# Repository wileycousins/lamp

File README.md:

# lamp
Another object from [Wiley Cousins](https://wileycousins.com) and [Trig Projects](http://trigprojects.com)

Lamp is a smart LED lamp system that has two jobs: letting you know about things and looking pretty. Currently in development.

## requirements
* Node.js
* Foreman

## setup
    npm install

## running
    foreman start

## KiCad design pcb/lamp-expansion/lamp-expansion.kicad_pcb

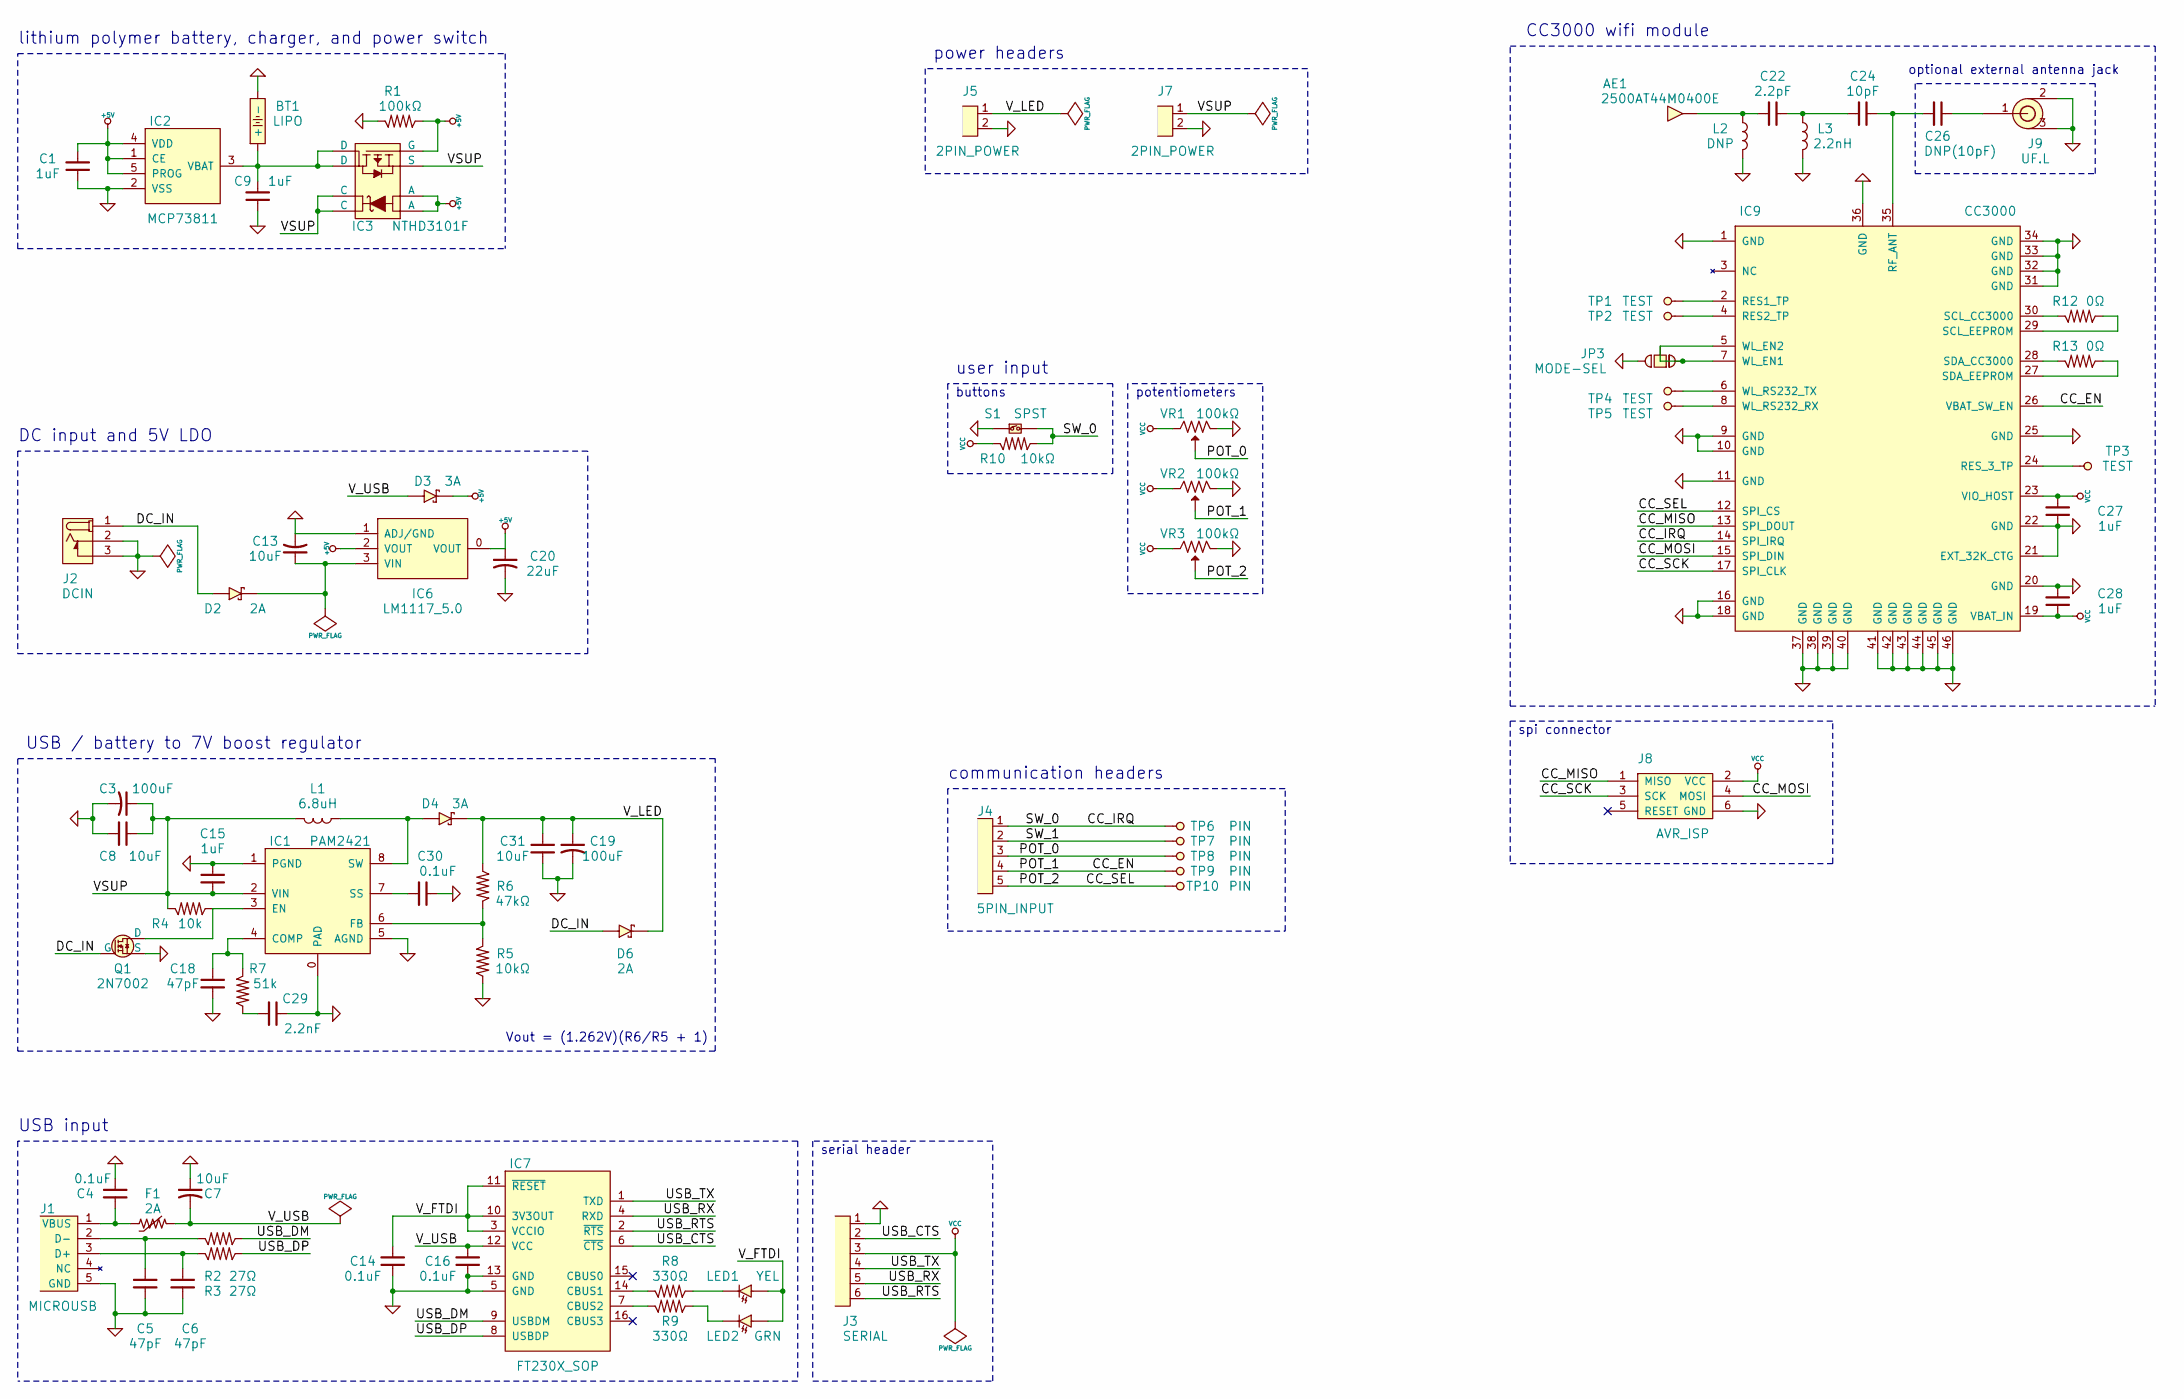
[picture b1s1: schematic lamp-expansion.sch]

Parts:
AE1: 2500AT44M0400E; Manuf. Part 2500AT44M0400E
BT1: LIPO
C1, C9, C15, C27, C28: 1uF
C3, C19: 100uF; Manuf. Part EMVA160ADA101MF55G
C4, C14, C16, C30: 0.1uF
C5, C6, C18: 47pF
C7: 10uF; Manuf. Part Taiyo Yuden
C8, C31: 10uF
C13: 10uF; Manuf. Part TMK316F106ZL-T
C20: 22uF; Manuf. Part LMK316F226ZL-T
C22: 2.2pF
C24: 10pF
C26: DNP(10pF)
C29: 2.2nF
D2, D6: 2A; Manuf. Part MSS2P2-M3/89A
D3, D4: 3A; Manuf. Part RB056L-40TE25
F1: 2A
IC1: PAM2421
IC2: MCP73811; Manuf. Part MCP73811T-420I/OT
IC3: NTHD3101F
IC6: LM1117_5.0; Manuf. Part AZ1117CH-5.0TRG1
IC7: FT230X_SOP
IC9: CC3000; Manuf. Part CC3000MOD
J1: MICROUSB
J2: DCIN
J3: SERIAL
J4: 5PIN_INPUT
J5, J7: 2PIN_POWER
J8: AVR_ISP
J9: UF.L
JP3: MODE-SEL
L1: 6.8uH; Manuf. Part SRN6045-6R8Y
L2: DNP
L3: 2.2nH
LED1: YEL
LED2: GRN
Q1: 2N7002; Manuf. Part 2N7002P,215
R1: 100kΩ
R2, R3: 27Ω
R4: 10k
R5, R10: 10kΩ
R6: 47kΩ
R7: 51k
R8, R9: 330Ω
R12, R13: 0Ω
S1: SPST
TP1, TP2, TP3, TP4, TP5: TEST
TP6, TP7, TP8, TP9, TP10: PIN
VR1, VR2, VR3: 100kΩ; Manuf. Part PTA2043-2015CPB103

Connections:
+5V: C1.1, C20.1, D3.1 (C), IC2.1 (CE), IC2.4 (VDD), IC2.5 (PROG), IC3.1 (A), IC3.2 (A), IC3.4 (G), IC6.0 (VOUT), IC6.2 (VOUT), R1.2
/CC_EN: IC9.26 (VBAT_SW_EN), J4.4, TP9.1, VR2.2 (W)
/CC_IRQ: IC9.14 (SPI_IRQ), J4.1, R10.2, S1.2, TP6.1
/CC_MISO: IC9.13 (SPI_DOUT), J8.1 (MISO)
/CC_MOSI: IC9.15 (SPI_DIN), J8.4 (MOSI)
/CC_SCK: IC9.17 (SPI_CLK), J8.3 (SCK)
/CC_SEL: IC9.12 (SPI_CS), J4.5, TP10.1, VR3.2 (W)
/DC_IN: D2.2 (A), D6.2 (A), J2.1 (POLE), Q1.1 (G)
/POT_0: J4.3, TP8.1, VR1.2 (W)
/SW_1: J4.2, TP7.1
/USB_CTS: IC7.6 (~CTS~), J3.2
/USB_DM: IC7.9 (USBDM), R2.2
/USB_DP: IC7.8 (USBDP), R3.2
/USB_RTS: IC7.2 (~RTS~), J3.6
/USB_RX: IC7.4 (RXD), J3.5
/USB_TX: IC7.1 (TXD), J3.4
/VSUP: C3.1, C8.1, C15.2, IC1.2 (VIN), IC3.3 (S), IC3.7 (C), IC3.8 (C), J7.1, L1.2, R4.1
/V_FTDI: C14.1, IC7.3 (VCCIO), IC7.10 (3V3OUT), IC7.11 (~RESET~), LED1.2 (A), LED2.2 (A)
/V_LED: C19.1, C31.1, D4.1 (C), D6.1 (C), J5.1, R6.2
/V_USB: C7.2, C16.1, D3.2 (A), F1.2, IC7.12 (VCC)
GND: BT1.2 (-), C1.2, C3.2, C4.1, C5.2, C6.2, C7.1, C8.2, C9.2, C13.2, C14.2, C15.1, C16.2, C18.2, C19.2, C20.2, C27.2, C28.1, C29.1, C30.2, C31.2, IC1.0 (PAD), IC1.1 (PGND), IC1.5 (AGND), IC2.2 (VSS), IC6.1 (ADJ/GND), IC7.5 (GND), IC7.13 (GND), IC9.1 (GND), IC9.9 (GND), IC9.10 (GND), IC9.11 (GND), IC9.16 (GND), IC9.18 (GND), IC9.20 (GND), IC9.21 (EXT_32K_CTG), IC9.22 (GND), IC9.25 (GND), IC9.31 (GND), IC9.32 (GND), IC9.33 (GND), IC9.34 (GND), IC9.36 (GND), IC9.37 (GND), IC9.38 (GND), IC9.39 (GND), IC9.40 (GND), IC9.41 (GND), IC9.42 (GND), IC9.43 (GND), IC9.44 (GND), IC9.45 (GND), IC9.46 (GND), J1.5 (GND), J2.2 (OUT), J2.3 (OUT), J3.1, J5.2, J7.2, J8.6 (GND), J9.2, J9.3, JP3.3, L2.2, L3.2, Q1.2 (S), R1.1, R5.2, S1.1, VR1.3 (E2), VR2.3 (E2), VR3.3 (E2)
unnamed: AE1.1, C22.1, L2.1
unnamed: BT1.1 (+), C9.1, IC2.3 (VBAT), IC3.5 (D), IC3.6 (D)
unnamed: C4.2, F1.1, J1.1 (VBUS)
unnamed: C5.1, J1.2 (D-), R2.1
unnamed: C6.1, J1.3 (D+), R3.1
unnamed: C13.1, D2.1 (C), IC6.3 (VIN)
unnamed: C18.1, IC1.4 (COMP), R7.1
unnamed: C22.2, C24.2, L3.1
unnamed: C24.1, C26.1, IC9.35 (RF_ANT)
unnamed: C26.2, J9.1 (CENTER)
unnamed: C29.2, R7.2
unnamed: C30.1, IC1.7 (SS)
unnamed: D4.2 (A), IC1.8 (SW), L1.1
unnamed: IC1.3 (EN), Q1.3 (D), R4.2
unnamed: IC1.6 (FB), R5.1, R6.1
unnamed: IC7.7 (CBUS2), R9.1
unnamed: IC7.14 (CBUS1), R8.1
unnamed: IC9.2 (RES1_TP), TP1.1
unnamed: IC9.4 (RES2_TP), TP2.1
unnamed: IC9.5 (WL_EN2), IC9.7 (WL_EN1), JP3.1, JP3.2
unnamed: IC9.6 (WL_RS232_TX), TP4.1
unnamed: IC9.8 (WL_RS232_RX), TP5.1
unnamed: IC9.24 (RES_3_TP), TP3.1
unnamed: IC9.27 (SDA_EEPROM), R13.2
unnamed: IC9.28 (SDA_CC3000), R13.1
unnamed: IC9.29 (SCL_EEPROM), R12.2
unnamed: IC9.30 (SCL_CC3000), R12.1
unnamed: LED1.1 (C), R8.2
unnamed: LED2.1 (C), R9.2
VCC: C27.1, C28.2, IC9.19 (VBAT_IN), IC9.23 (VIO_HOST), J3.3, J8.2 (VCC), R10.1, VR1.1 (E1), VR2.1 (E1), VR3.1 (E1)

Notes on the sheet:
USB input
DC input and 5V LDO
lithium polymer battery, charger, and power switch
optional external antenna jack
CC3000 wifi module
spi connector
USB / battery to 7V boost regulator
power headers
serial header
potentiometers
buttons
user input
Vout = (1.262V)(R6/R5 + 1)
communication headers

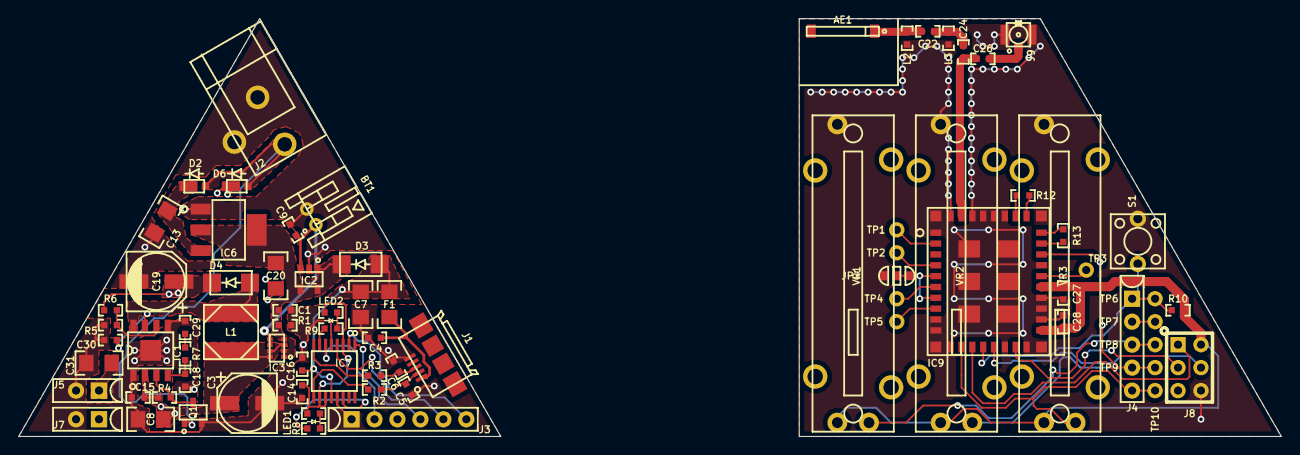
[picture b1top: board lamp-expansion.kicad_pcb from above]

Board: 2 copper layers, 139.7 x 46.2 mm, 77 parts (0 on the bottom side), 51 nets.

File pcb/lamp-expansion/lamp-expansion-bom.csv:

Source:,/media/sf_projects/lamp/pcb/lamp-expansion/lamp-expansion.sch
Date:,Fri 15 Aug 2014 06:17:15 PM CDT
Tool:,Eeschema (2014-04-22 BZR 4817)-product
Component Count:,67

Individual Components:

Item,Qty,Reference(s),Value,LibPart,Footprint,Datasheet,Distrib. Part,Distributor,Manuf. Part,Manufacturer
,,AE1,2500AT44M0400E,standard:ANTENNA,,,712-1403-1-ND,Digikey,2500AT44M0400E,Johanson Technology Inc
,,BT1,LIPO,connector:LIPO,,,,,,
,,C1,1uF,standard:C,,,,,,
,,C13,10uF,standard:C_POL,,,587-1353-1-ND,Digikey,TMK316F106ZL-T,Taiyo Yuden
,,C14,0.1uF,standard:C,,,,,,
,,C15,1uF,standard:C,,,,,,
,,C16,0.1uF,standard:C,,,,,,
,,C18,47pF,standard:C,,,,,,
,,C19,100uF,standard:C_POL,,,565-2089-1-ND,Digikey,EMVA160ADA101MF55G,United Chemi-Con
,,C20,22uF,standard:C_POL,,,587-1356-1-ND,Digikey,LMK316F226ZL-T,Taiyo Yuden
,,C22,2.2pF,standard:C,,,,,,
,,C24,10pF,standard:C,,,,,,
,,C26,DNP(10pF),standard:C,,,,,,
,,C27,1uF,standard:C,,,,,,
,,C28,1uF,standard:C,,,,,,
,,C29,2.2nF,standard:C,,,,,,
,,C3,100uF,standard:C_POL,,,565-2089-1-ND,Digikey,EMVA160ADA101MF55G,United Chemi-Con
,,C30,0.1uF,standard:C,,,,,,
,,C31,10uF,standard:C,,,,,,
,,C4,0.1uF,standard:C,,,,,,
,,C5,47pF,standard:C,,,,,,
,,C6,47pF,standard:C,,,,,,
,,C7,10uF,standard:C_POL,,,587-1353-1-ND,Digikey,Taiyo Yuden,TMK316F106ZL-T
,,C8,10uF,standard:C,,,,,,
,,C9,1uF,standard:C,,,,,,
,,D2,2A,standard:D_SCHOTTKY,,,MSS2P2-M3/89AGICT-ND,Digikey,MSS2P2-M3/89A,Vishay
,,D3,3A,standard:D_SCHOTTKY,,,RB056L-40TE25CT-ND,Digikey,RB056L-40TE25,Rohm Semiconductor
,,D4,3A,standard:D_SCHOTTKY,,,RB056L-40TE25CT-ND,Digikey,RB056L-40TE25,Rohm Semiconductor
,,D6,2A,standard:D_SCHOTTKY,,,MSS2P2-M3/89AGICT-ND,Digikey,MSS2P2-M3/89A,Vishay
,,F1,2A,standard:PTC,,,,,,
,,IC1,PAM2421,diode-inc-ic:PAM242X,,,,,,Diodes Inc
,,IC2,MCP73811,microchip-ic:MCP73811/2,,,MCP73811T-420I/OTCT-ND,Digikey,MCP73811T-420I/OT,Microchip Technology
,,IC3,NTHD3101F,on-semi-ic:NTHD3101F,,,,,,On Semiconductor
,,IC6,LM1117_5.0,regulator:LM1117,,,AZ1117CH-5.0TRG1DICT-ND,Digikey,AZ1117CH-5.0TRG1,Diodes Incorporated
,,IC7,FT230X_SOP,ftdi-ic:FT230X_SOP,,,,,,
,,IC9,CC3000,ti-ic:CC3000,,http://www.ti.com/lit/gpn/cc3000,296-35512-1-ND,Digikey,CC3000MOD,TI
,,J1,MICROUSB,connector:MICROUSB,,,,,,
,,J2,DCIN,connector:DC-BARREL-JACK,,,,,,
,,J3,SERIAL,connector:6PIN_FEMALE,,,,,,
,,J4,5PIN_INPUT,connector:5PIN_FEMALE,,,,,,
,,J5,2PIN_POWER,connector:2PIN_FEMALE,,,,,,
,,J7,2PIN_POWER,connector:2PIN_FEMALE,,,,,,
,,J8,AVR_ISP,avr-mcu:AVR_ISP,,,,,,
,,J9,UF.L,connector:COAX-JACK,,,,,,
,,JP3,MODE-SEL,standard:JUMPER_3-PIN,,,,,,
,,L1,6.8uH,standard:L,,,SRN6045-6R8YCT-ND,Digikey,SRN6045-6R8Y,Bourns Inc
,,L2,DNP,standard:L,,,,,,
,,L3,2.2nH,standard:L,,,,,,
,,LED1,YEL,standard:LED,,,,,,
,,LED2,GRN,standard:LED,,,,,,
,,Q1,2N7002,transistor:N-CHAN-MOSFET_SOT,,,568-5818-1-ND,Digikey,"2N7002P,215",NXP

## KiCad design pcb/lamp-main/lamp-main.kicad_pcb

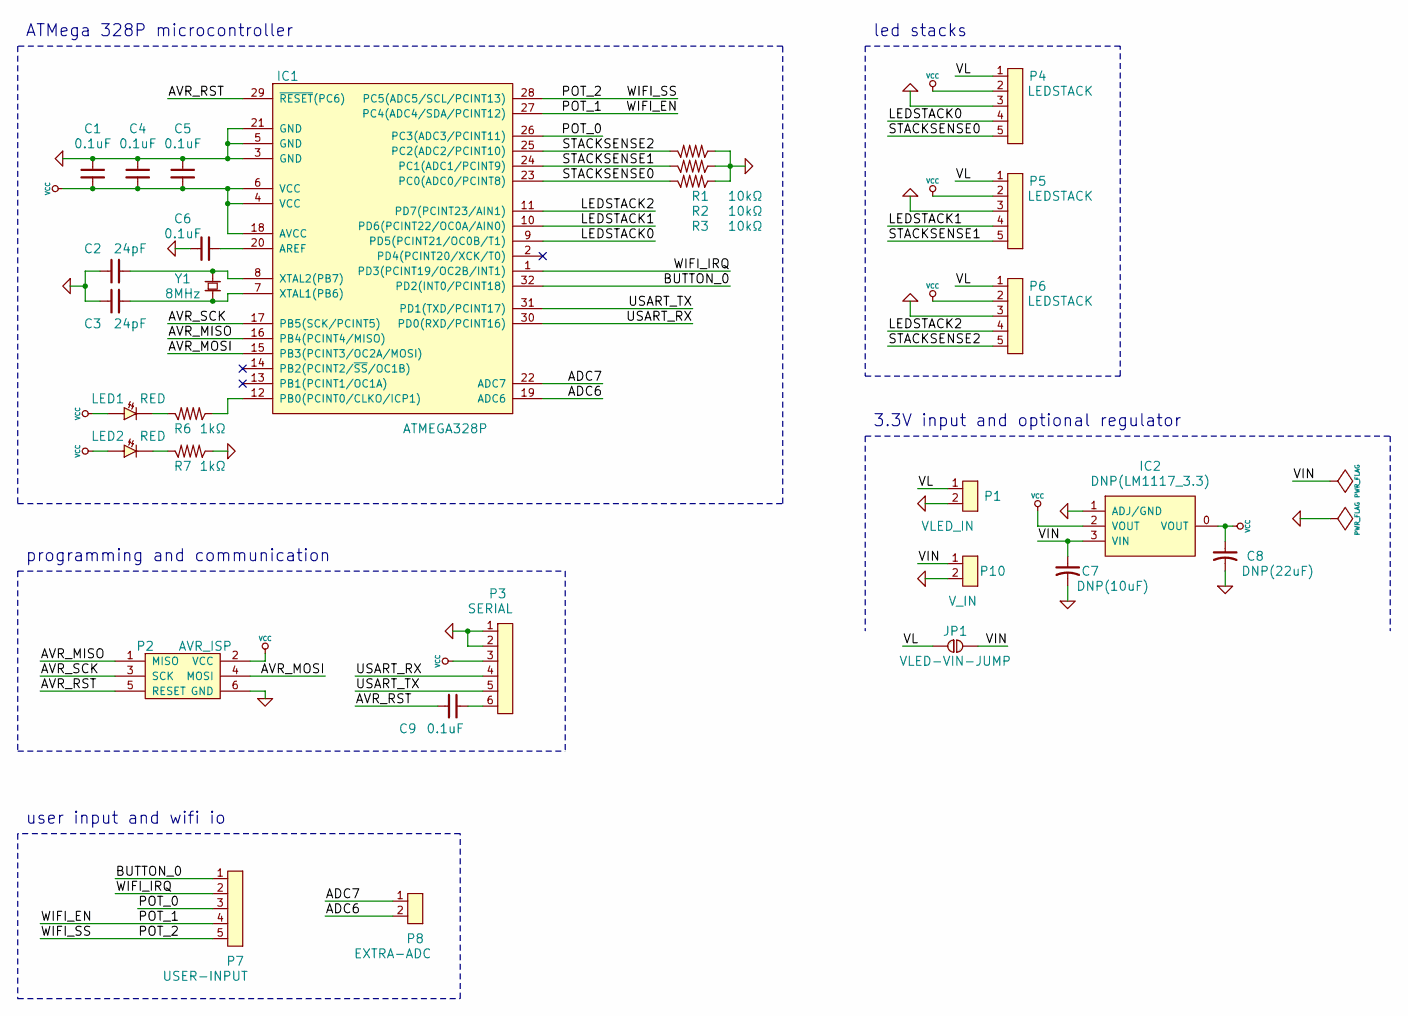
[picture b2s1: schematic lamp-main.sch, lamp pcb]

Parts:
C1, C4, C5, C6, C9: 0.1uF
C2, C3: 24pF; Manuf. Part CL10C240JB8NCNC
C7: DNP(10uF); Manuf. Part TMK316F106ZL-T
C8: DNP(22uF); Manuf. Part LMK316F226ZL-T
IC1: ATMEGA328P; Manufacturer Part ATMEGA328P-AU
IC2: DNP(LM1117_3.3); Manuf. Part AZ1117CH-5.0TRG1
JP1: VLED-VIN-JUMP
LED1, LED2: RED
P1: VLED_IN
P2: AVR_ISP
P3: SERIAL
P4, P5, P6: LEDSTACK
P7: USER-INPUT
P8: EXTRA-ADC
P10: V_IN
R1, R2, R3: 10kΩ
R6, R7: 1kΩ
Y1: 8MHz; Manuf. Part ABM2-8.000MHZ-D4Y-T

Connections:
/ADC6: IC1.19 (ADC6), P8.2
/ADC7: IC1.22 (ADC7), P8.1
/AVR_MISO: IC1.16 (PB4(PCINT4/MISO)), P2.1 (MISO)
/AVR_MOSI: IC1.15 (PB3(PCINT3/OC2A/MOSI)), P2.4 (MOSI)
/AVR_RST: C9.1, IC1.29 (~RESET~(PC6)), P2.5 (RESET)
/AVR_SCK: IC1.17 (PB5(SCK/PCINT5)), P2.3 (SCK)
/BUTTON_0: IC1.32 (PD2(INT0/PCINT18)), P7.1
/LEDSTACK0: IC1.9 (PD5(PCINT21/OC0B/T1)), P4.4
/LEDSTACK1: IC1.10 (PD6(PCINT22/OC0A/AIN0)), P5.4
/LEDSTACK2: IC1.11 (PD7(PCINT23/AIN1)), P6.4
/POT_0: IC1.26 (PC3(ADC3/PCINT11)), P7.3
/POT_1: IC1.27 (PC4(ADC4/SDA/PCINT12)), P7.4
/POT_2: IC1.28 (PC5(ADC5/SCL/PCINT13)), P7.5
/STACKSENSE0: IC1.23 (PC0(ADC0/PCINT8)), P4.5, R3.1
/STACKSENSE1: IC1.24 (PC1(ADC1/PCINT9)), P5.5, R2.1
/STACKSENSE2: IC1.25 (PC2(ADC2/PCINT10)), P6.5, R1.1
/USART_RX: IC1.30 (PD0(RXD/PCINT16)), P3.4
/USART_TX: IC1.31 (PD1(TXD/PCINT17)), P3.5
/VIN: C7.1, IC2.3 (VIN), JP1.2, P10.1
/VL: JP1.1, P1.1, P4.1, P5.1, P6.1
/WIFI_IRQ: IC1.1 (PD3(PCINT19/OC2B/INT1)), P7.2
GND: C1.2, C2.1, C3.1, C4.2, C5.2, C6.1, C7.2, C8.2, IC1.3 (GND), IC1.5 (GND), IC1.21 (GND), IC2.1 (ADJ/GND), P1.2, P2.6 (GND), P3.1, P3.2, P4.3, P5.3, P6.3, P10.2, R1.2, R2.2, R3.2, R7.2
unnamed: C2.2, IC1.8 (XTAL2(PB7)), Y1.2
unnamed: C3.2, IC1.7 (XTAL1(PB6)), Y1.1
unnamed: C6.2, IC1.20 (AREF)
unnamed: C9.2, P3.6
unnamed: IC1.12 (PB0(PCINT0/CLKO/ICP1)), R6.2
unnamed: LED1.1 (C), R6.1
unnamed: LED2.1 (C), R7.1
VCC: C1.1, C4.1, C5.1, C8.1, IC1.4 (VCC), IC1.6 (VCC), IC1.18 (AVCC), IC2.0 (VOUT), IC2.2 (VOUT), LED1.2 (A), LED2.2 (A), P2.2 (VCC), P3.3, P4.2, P5.2, P6.2

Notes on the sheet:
3.3V input and optional regulator
programming and communication
led stacks
ATMega 328P microcontroller
user input and wifi io

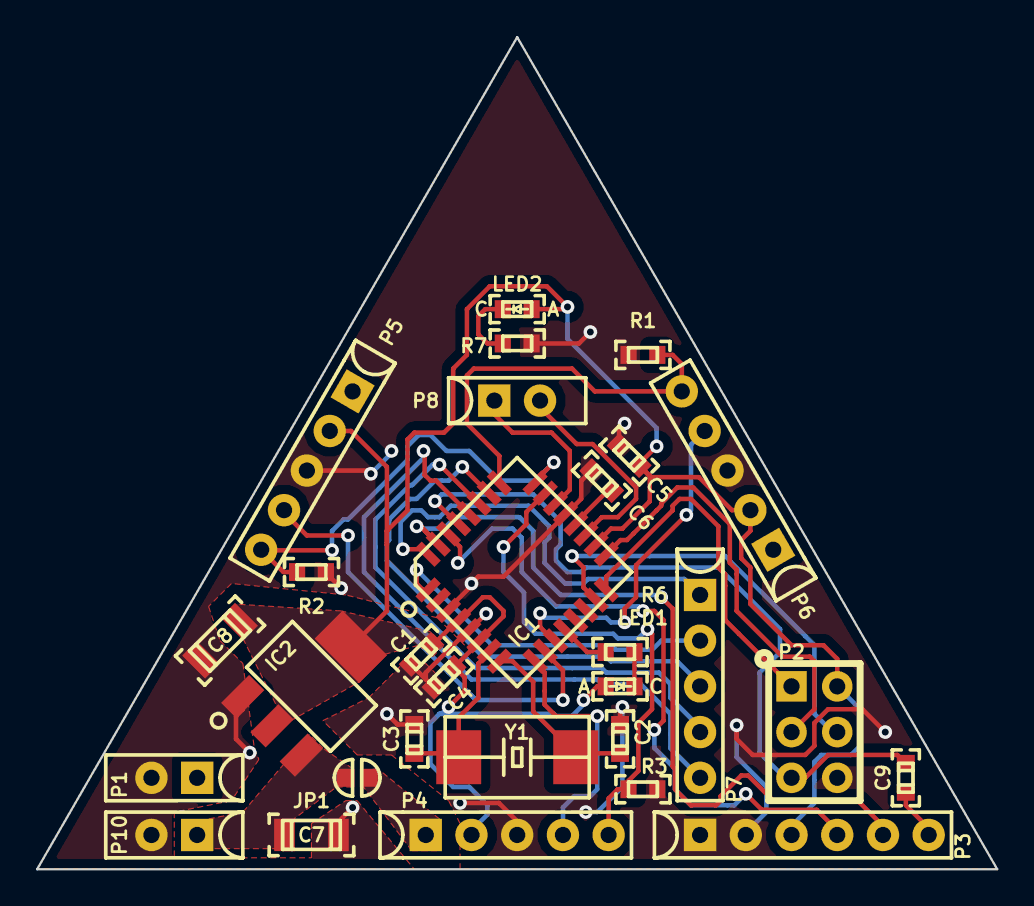
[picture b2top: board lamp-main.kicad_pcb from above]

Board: 2 copper layers, 53.3 x 46.2 mm, 29 parts (0 on the bottom side), 30 nets.

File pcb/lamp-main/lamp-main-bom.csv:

Source:,/media/sf_projects/lamp/pcb/lamp-main/lamp-main.sch
Date:,Fri 15 Aug 2014 04:16:45 PM CDT
Tool:,eeschema (2014-03-19 BZR 4756)-product
Component Count:,29

Individual Components:

Item,Qty,Reference(s),Value,LibPart,Footprint,Datasheet,Distrib. Link,Distrib. Part,Distributor,Manuf. Part,Manufacturer
,,C1,0.1uF,standard:C,capacitor:0603(1608m)-CHIP-CAP,,,,On Hand,,
,,C2,24pF,standard:C,capacitor:0603(1608m)-CHIP-CAP,,http://www.digikey.com/product-detail/en/CL10C240JB8NCNC/127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,1276-2242-1-ND,Digikey,CL10C240JB8NCNC,Samsung
,,C3,24pF,standard:C,capacitor:0603(1608m)-CHIP-CAP,,http://www.digikey.com/product-detail/en/CL10C240JB8NCNC/127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,1276-2242-1-ND,Digikey,CL10C240JB8NCNC,"Samsung Electro-Mechanics America, Inc"
,,C4,0.1uF,standard:C,capacitor:0603(1608m)-CHIP-CAP,,,,On hand,,
,,C5,0.1uF,standard:C,capacitor:0603(1608m)-CHIP-CAP,,,,On hand,,
,,C6,0.1uF,standard:C,capacitor:0603(1608m)-CHIP-CAP,,,,On hand,,
,,C7,DNP(10uF),standard:C_POL,capacitor:1206(3216m)-CHIP-CAP,,http://www.digikey.com/product-detail/en/TMK316F106ZL-T/587-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,587-1353-1-ND,Digikey,TMK316F106ZL-T,Taiyo Yuden
,,C8,DNP(22uF),standard:C_POL,capacitor:1206(3216m)-CHIP-CAP,,http://www.digikey.com/product-detail/en/LMK316F226ZL-T/587-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,587-1356-1-ND,Digikey,LMK316F226ZL-T,Taiyo Yuden
,,C9,0.1uF,standard:C,capacitor:0603(1608m)-CHIP-CAP,,,,On hand,,
,,IC1,ATMEGA328P,avr-mcu:ATMEGA328P_TQFP,qfp:TQFP32_P0.8mm,,http://www.digikey.com/product-detail/en/ATMEGA328P-AU/ATMEG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,ATMEGA328P-AU-ND,Digikey,ATMEGA328P-AU,Atmel
,,IC2,DNP(LM1117_3.3),lamp-main-cache:LM1117,sot:SOT223,http://www.diodes.com/datasheets/AZ1117C.pdf,http://www.digikey.com/product-detail/en/AZ1117CH-5.0TRG1/AZ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,AZ1117CH-5.0TRG1DICT-ND,Digikey,AZ1117CH-5.0TRG1,Diodes Incorporated
,,JP1,VLED-VIN-JUMP,standard:JUMPER_2-PIN,jumper:SOLDER-JUMPER_1-WAY,,,,,,
,,LED1,RED,standard:LED,led:0603(1608m)-SM-LED,,,,On hand,,
,,LED2,RED,standard:LED,led:0603(1608m)-SM-LED,,,,On hand,,
,,P1,VLED_IN,connector:2PIN_MALE,sip:SIP2,,,,,,
,,P10,V_IN,connector:2PIN_MALE,sip:SIP2,,,,,,
,,P2,AVR_ISP,avr-mcu:AVR_ISP,connect-thru:2x3-ARRAY_P100mil,,,,,,
,,P3,SERIAL,connector:6PIN_HEADER,sip:SIP6,,,,,,
,,P4,LEDSTACK,connector:5PIN_MALE,sip:SIP5,,,,,,
,,P5,LEDSTACK,connector:5PIN_MALE,sip:SIP5,,,,,,
,,P6,LEDSTACK,connector:5PIN_MALE,sip:SIP5,,,,,,
,,P7,USER-INPUT,connector:5PIN_MALE,sip:SIP5,,,,,,
,,P8,EXTRA-ADC,connector:2PIN_MALE,sip:SIP2,,,,,,

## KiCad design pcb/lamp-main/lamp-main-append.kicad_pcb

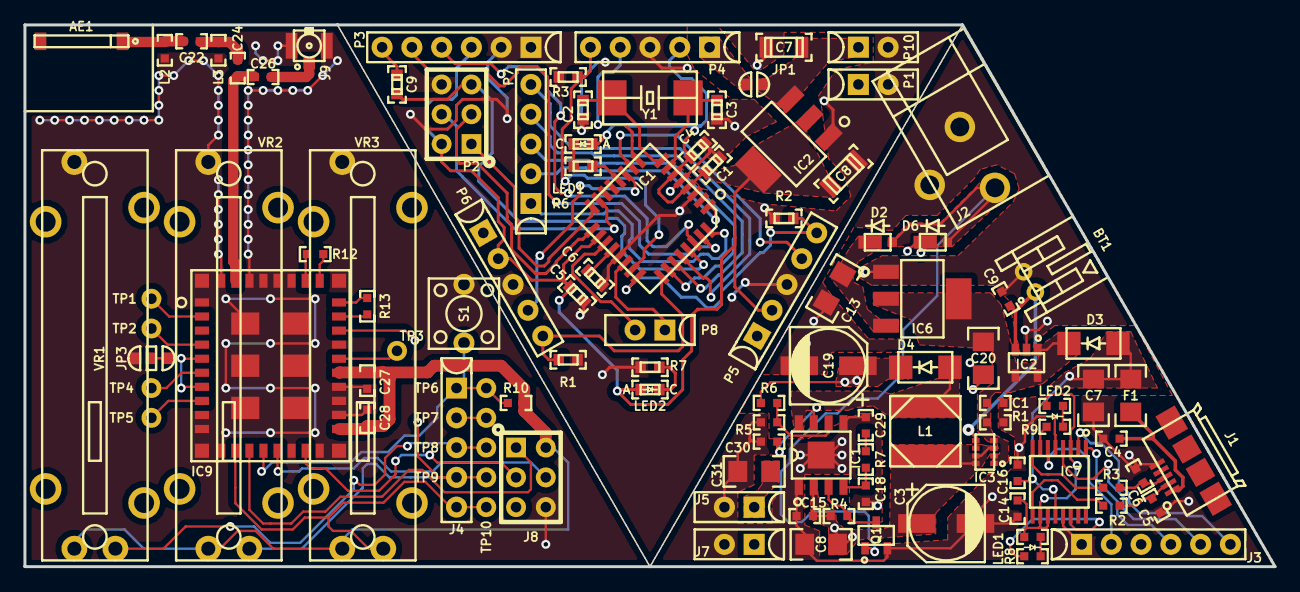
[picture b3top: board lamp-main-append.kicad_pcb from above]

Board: 2 copper layers, 106.7 x 46.2 mm, 106 parts (0 on the bottom side), 51 nets.

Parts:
AE1: 2500AT44M0400E; JOHANSON-2500AT44M0400_2.4GHz-chip-antenna
BT1: LIPO; JST-S2B-PH-K_right-angle-jack
C1, C9, C15, C27, C28: 1uF; 0603(1608m)
C1#2, C4#2, C5#2, C6#2, C9#2: 0.1uF; 0603(1608m)-CHIP-CAP
C2, C3#2: 24pF; 0603(1608m)-CHIP-CAP
C3, C19: 100uF; PANA-D_CHEMI-F_SM-ALUMINUM
C4, C14, C16, C30: 0.1uF; 0603(1608m)
C5, C6, C18: 47pF; 0603(1608m)
C7, C8, C13, C31: 10uF; 1206(3216m)
C7#2: DNP(10uF); 1206(3216m)-CHIP-CAP
C8#2: DNP(22uF); 1206(3216m)-CHIP-CAP
C20: 22uF; 1206(3216m)
C22: 2.2pF; 0603(1608m)
C24: 10pF; 0603(1608m)
C26: DNP(10pF); 0603(1608m)
C29: 2.2nF; 0603(1608m)
D2, D6: 2A; MICROSMP
D3, D4: 3A; DO-214AC
F1: 2A; 1206(3216m)
IC1: PAM2421; SOP8_ep
IC1#2: ATMEGA328P; TQFP32_P0.8mm
IC2: MCP73811; SOT23-5
IC2#2: DNP(LM1117_3.3); SOT223
IC3: NTHD3101F; CHIPFET-1206-8
IC6: LM1117_5.0; SOT223
IC7: FT230X_SOP; SSOP16
IC9: CC3000
J1: MICROUSB; MICROUSB_sm
J2: DCIN; CUI-PJ-102A_dc-barrel-jack
J3: SERIAL; SIP6
J4: 5PIN_INPUT; SIP5
J5, J7: 2PIN_POWER; SIP2
J8: AVR_ISP; 2x3-ARRAY_P100mil
J9: UF.L; U.FL-COAX
JP1: VLED-VIN-JUMP; SOLDER-JUMPER_1-WAY
JP3: MODE-SEL; SOLDER-JUMPER_2-WAY
L1: 6.8uH; SM-INDUCTOR_6mmX6mm
L2: DNP; 0603(1608m)
L3: 2.2nH; 0603(1608m)
LED1: YEL; 0603(1608m)-SM-LED
LED1#2, LED2#2: RED; 0603(1608m)-SM-LED
LED2: GRN; 0603(1608m)-SM-LED
P1: VLED_IN; SIP2
P2: AVR_ISP; 2x3-ARRAY_P100mil
P3: SERIAL; SIP6
P4, P5, P6: LEDSTACK; SIP5
P7: USER-INPUT; SIP5
P8: EXTRA-ADC; SIP2
P10: V_IN; SIP2
Q1: 2N7002; SOT23
R1: 100kΩ; 0603(1608m)
R1#2, R2#2, R3#2: 10kΩ; 0603(1608m)-CHIP-RESISTOR
R2, R3: 27Ω; 0603(1608m)
R4: 10k; 0603(1608m)
R5, R10: 10kΩ; 0603(1608m)
R6: 47kΩ; 0603(1608m)
R6#2, R7#2: 1kΩ; 0603(1608m)-CHIP-RESISTOR
R7: 51k; 0603(1608m)
R8, R9: 330Ω; 0603(1608m)
R12, R13: 0Ω; 0603(1608m)
S1: SPST; SPST-2-PIN_6mm_thru
TP1, TP2, TP3, TP4, TP5: TEST; 1-PIN
TP6, TP7, TP8, TP9, TP10: PIN; 1-PIN
VR1, VR2, VR3: 100kΩ; BOURNS-PTA2043_20mm-slide-pot
Y1: 8MHz; ABRACON-ABM2_xtal

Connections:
+5V: C1.1, C1#2.1, C4#2.1, C5#2.1, C8#2.1, C20.1, D3.1, IC1#2.4, IC1#2.6, IC1#2.18, IC2.1, IC2.4, IC2.5, IC2#2.0, IC2#2.2, IC3.1, IC3.2, IC3.4, IC6.0, IC6.2, LED1#2.2, LED2#2.2, P2.2, P3.3, P4.2, P5.2, P6.2, R1.2
/CC_EN: C1#2.2, C2.1, C3#2.1, C4#2.2, C5#2.2, C6#2.1, C7#2.2, C8#2.2, IC1#2.3, IC1#2.5, IC1#2.21, IC2#2.1, IC9.26, J4.4, P1.2, P2.6, P3.1, P3.2, P4.3, P5.3, P6.3, P10.2, R1#2.2, R2#2.2, R3#2.2, R7#2.2, TP9.1, VR2.2
/CC_IRQ: C2.2, IC1#2.8, IC9.14, J4.1, R10.2, S1.2, TP6.1, Y1.2
/CC_MISO: C3#2.2, IC1#2.7, IC9.13, J8.1, Y1.1
/CC_MOSI: C6#2.2, IC1#2.20, IC9.15, J8.4
/CC_SCK: C7#2.1, IC2#2.3, IC9.17, J8.3, JP1.2, P10.1
/CC_SEL: C9#2.1, IC1#2.29, IC9.12, J4.5, P2.5, TP10.1, VR3.2
/DC_IN: C9#2.2, D2.2, D6.2, J2.1, P3.6, Q1.1
/POT_0: IC1#2.32, J4.3, P7.1, TP8.1, VR1.2
/SW_1: IC1#2.9, J4.2, P4.4, TP7.1
/USB_CTS: IC1#2.10, IC7.6, J3.2, P5.4
/USB_DM: IC1#2.11, IC7.9, P6.4, R2.2
/USB_DP: IC1#2.12, IC7.8, R3.2, R6#2.2
/USB_RTS: IC1#2.15, IC7.2, J3.6, P2.4
/USB_RX: IC1#2.16, IC7.4, J3.5, P2.1
/USB_TX: IC1#2.17, IC7.1, J3.4, P2.3
/VSUP: C3.1, C8.1, C15.2, IC1.2, IC3.3, IC3.7, IC3.8, J7.1, L1.2, R4.1
/V_FTDI: C14.1, IC1#2.27, IC7.3, IC7.10, IC7.11, LED1.2, LED2.2, P7.4
/V_LED: C19.1, C31.1, D4.1, D6.1, IC1#2.28, J5.1, P7.5, R6.2
/V_USB: C7.2, C16.1, D3.2, F1.2, IC1#2.23, IC7.12, P4.5, R3#2.1
GND: BT1.2, C1.2, C3.2, C4.1, C5.2, C6.2, C7.1, C8.2, C9.2, C13.2, C14.2, C15.1, C16.2, C18.2, C19.2, C20.2, C27.2, C28.1, C29.1, C30.2, C31.2, IC1.0, IC1.1, IC1.5, IC1#2.24, IC2.2, IC6.1, IC7.5, IC7.13, IC9.1, IC9.9, IC9.10, IC9.11, IC9.16, IC9.18, IC9.20, IC9.21, IC9.22, IC9.25, IC9.31, IC9.32, IC9.33, IC9.34, IC9.36, IC9.37, IC9.38, IC9.39, IC9.40, IC9.41, IC9.42, IC9.43, IC9.44, IC9.45, IC9.46, J1.5, J2.2, J3.1, J5.2, J7.2, J8.6, J9.2, J9.3, JP3.3, L2.2, L3.2, P5.5, Q1.2, R1.1, R2#2.1, R5.2, S1.1, VR1.3, VR2.3, VR3.3
unnamed: AE1.1, C22.1, IC1#2.25, L2.1, P6.5, R1#2.1
unnamed: BT1.1, C9.1, IC2.3, IC3.5, IC3.6
unnamed: C4.2, F1.1, IC1#2.13, J1.1
unnamed: C5.1, IC1#2.14, J1.2, R2.1
unnamed: C6.1, IC1#2.19, J1.3, P8.2, R3.1
unnamed: C13.1, D2.1, IC6.3
unnamed: C18.1, IC1.4, IC1#2.26, P7.3, R7.1
unnamed: C22.2, C24.2, IC1#2.30, L3.1, P3.4
unnamed: C24.1, C26.1, IC1#2.31, IC9.35, P3.5
unnamed: C26.2, J9.1, LED1#2.1, R6#2.1
unnamed: C29.2, LED2#2.1, R7.2, R7#2.1
unnamed: C30.1, IC1.7, IC1#2.2
unnamed: D4.2, IC1.8, IC1#2.22, L1.1, P8.1
unnamed: IC1.3, JP1.1, P1.1, P4.1, P5.1, P6.1, Q1.3, R4.2
unnamed: IC1.6, IC1#2.1, P7.2, R5.1, R6.1
unnamed: IC7.7, R9.1
unnamed: IC7.14, R8.1
unnamed: IC9.2, TP1.1
unnamed: IC9.4, TP2.1
unnamed: IC9.5, IC9.7, JP3.1, JP3.2
unnamed: IC9.6, TP4.1
unnamed: IC9.8, TP5.1
unnamed: IC9.24, TP3.1
unnamed: IC9.27, R13.2
unnamed: IC9.28, R13.1
unnamed: IC9.29, R12.2
unnamed: IC9.30, R12.1
unnamed: LED1.1, R8.2
unnamed: LED2.1, R9.2
VCC: C27.1, C28.2, IC9.19, IC9.23, J3.3, J8.2, R10.1, VR1.1, VR2.1, VR3.1

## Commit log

2014-02-25 towel obtained
2014-02-25 basic README
2014-02-25 basic LICENSE
2014-02-26 kicad project file
2014-02-26 component libraries loaded
2014-02-26 schematic page formatting
2014-02-26 MCU set up with programming and serial headers
2014-02-26 got an led driver on there
2014-02-26 put a basic volatge regulator on there. may switch it out for something else
2014-02-27 first pass at schematic done
2014-02-27 stopping point because of new kicad library issues
2014-02-28 footprint selection done; moving to layout
2014-02-28 schematic pdf
2014-02-28 board geometry mostly figured out
2014-03-05 component positions good. need some mounting holes
2014-03-05 mounting holes
2014-03-05 laying traces
2014-03-05 layout going well but computer dying
2014-03-06 layout done. getting quotes then gonna clean up
2014-03-06 got some panelization going on for quotes
2014-03-06 done with work for the night
2014-03-06 adding some first pass gerbers. probably not good for actual fab, but sizing is right for quoting
2014-03-06 silkscreen cleaned up. need to figure out how I actually want to panelize
2014-03-06 i like this panelization layout
2014-03-13 full panel
2014-03-13 jk roflcopter. panel is now correct
2014-03-13 ok this might've finally got it
2014-03-13 fixed up board outline and fills
2014-03-13 panel plot
2014-03-13 new barebones plots
2014-03-13 barebones readme
2014-03-13 barebones order placed
2014-03-13 adding bom
2014-03-13 fixing up a few minor bom issues
2014-03-20 add first firmware files
2014-03-20 blink heartbeat led
2014-03-21 it's alive and my eyes hurt! @hcwiley
2014-03-21 cycle through colors
2014-03-21 add missing no-connect to avr pin
2014-03-21 add unused pin initilization
2014-03-21 implement led stack size sensing
2014-03-21 does not work in hardware
2014-03-21 stack sense correctly senses number of cards in stack
2014-03-21 verify that arrays are being calloced correctly and new set function works
2014-03-22 struggle bus
2014-03-22 slow but steady progress
2014-03-22 adjust data stream according to number of cards (finally)
2014-03-22 done with arduino testing sketch
2014-03-22 send data to all stacks with cards
2014-03-22 pumpz up the jamz
2014-03-26 about to go to SBSS
2014-03-30 cleanup variables
2014-03-31 figure out how to stop making this commit
2014-04-02 barebones twitter streamer working
2014-04-02 got basic mail watcher working
2014-04-02 tweet tracking updates
2014-04-02 made an index page. twitter login. w00t
2014-04-02 when you auth through twitter it starts a twitter streamer for you!
2014-04-02 i have no idea why my twitter stream is now just giving me my user obj
2014-04-02 fixed all the problems
2014-04-03 tweeter page looking pretty good. streaming working. i like this. tags addable
2014-04-03 remove tags
2014-04-03 updates to twitter tag add/remove
2014-04-03 updates from live. lamp working on webfaction
2014-04-03 added null user checks
2014-04-03 more no user checks
2014-04-03 working on profile add more services
2014-04-03 updated deploy script
2014-04-03 need username in deploy
2014-04-03 got providers working in a basic way
2014-04-03 added google auth. w00t
2014-04-03 fix title comment in header file
2014-04-03 create classes for lamp structure and effects
2014-04-03 continue work
2014-04-04 commit to move work location
2014-04-04 working on mail stream feature. also added socket disconnect that stops tweet streamer when client disconnects
2014-04-04 use pm2
2014-04-04 updated index
2014-04-04 log file names
2014-04-04 start?
2014-04-04 pull on deploy. put the logs where they should be
2014-04-04 restart?
2014-04-04 logs go where you should be
2014-04-04 what the hell pm2
2014-04-04 come on logs
2014-04-04 what ever logs, be in that dir
2014-04-04 ok lets test the restart
2014-04-04 lets keep logging killed old streamer
2014-04-04 working on memory mgmt
2014-04-04 derp
2014-04-04 moving matrix class into arduino folder for testing
2014-04-04 matrix class appears to work
2014-04-04 abandoning work on TLC class for now
2014-04-04 about to see if this compiles
2014-04-04 move to arduino testing folder for testing
2014-04-05 hold effect works
2014-04-05 add swirl effect
2014-04-05 cleanup commented out old code
2014-04-05 add rainbow effect
2014-04-16 start separating control circuits from led circuits
2014-04-21 rearranging file locations
2014-04-21 this is going somewhere
2014-04-21 move expansion board to separate project
2014-04-22 schematic work for expansion board
2014-04-22 work in progress
2014-04-22 cc3000 schematic diagram done
2014-04-22 moving to work on main board
2014-04-22 main board edits first pass done
2014-04-23 still need to add boost reg to schematic;
2014-04-23 expansion schematic nearly done
2014-04-23 i think the schematic is done
2014-04-30 schematic passes error checking
2014-04-30 ongoing footprint assignment
2014-04-30 kicad bug. building latest revision. hang on
2014-04-30 fixed typo for 74L05 LDO value
2014-05-01 assign footprints and start layout
2014-05-01 lets not stop the stream on disconnect
2014-05-01 log sending
2014-05-01 actually put it in the twitter section not emial
2014-05-01 more colors!
2014-05-02 replace boost regulator
2014-05-02 boost regulator work
2014-05-02 safety commit of project
2014-05-02 working on the layout;
2014-05-02 modules grouped in layout;
2014-05-02 moving over to main board
2014-05-02 redoing main layout
2014-05-02 add board outline
2014-05-02 trying something new
2014-05-02 refactor power supply configuration
2014-05-07 board layout and schematic refinement
2014-05-07 a little more room fort activities
2014-05-07 continue layout work
2014-05-08 layout and schematic refinements
2014-05-09 still working on the layout
2014-05-28 wire up main board
2014-05-28 still need to match nets up between main and expansion
2014-06-02 last few traces
2014-06-02 safety commit
2014-06-02 panelization
2014-10-15 several boards
2015-11-04 add changes found after first iMac powerup since 2014

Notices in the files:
pcb/lamp-main/lamp-main.sch:
copyright 2014 by Wiley Cousins
shared under the terms of the Creative Commons Attribution-ShareAlike 4.0 license
